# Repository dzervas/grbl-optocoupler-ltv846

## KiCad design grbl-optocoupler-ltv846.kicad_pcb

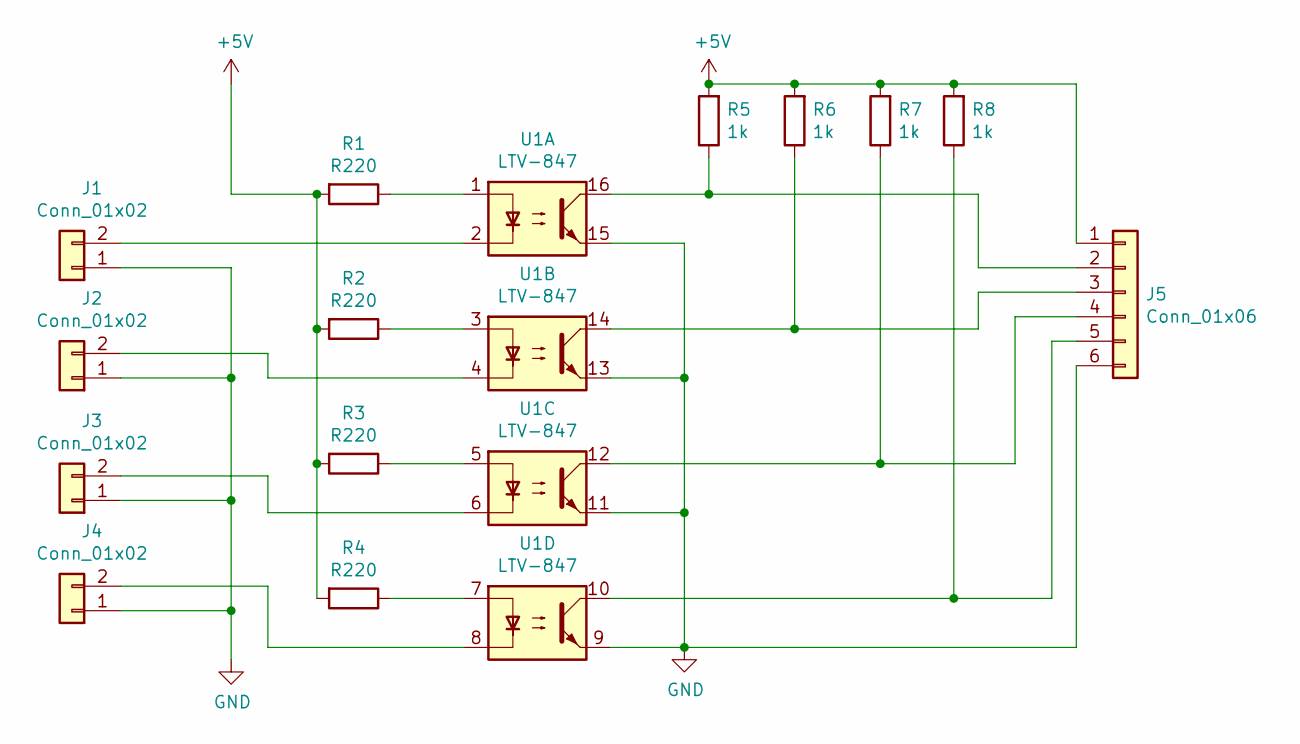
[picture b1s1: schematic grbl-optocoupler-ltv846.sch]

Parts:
J1, J2, J3, J4: Conn_01x02; PinHeader_1x02_P2.54mm_Vertical
J5: Conn_01x06; PinHeader_1x06_P2.54mm_Vertical
R1, R2, R3, R4: R220; R_Axial_DIN0207_L6.3mm_D2.5mm_P7.62mm_Horizontal
R5, R6, R7, R8: 1k; R_Axial_DIN0207_L6.3mm_D2.5mm_P7.62mm_Horizontal
U1: LTV-847; DIP-16_W7.62mm

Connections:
+5V: J5.1, R1.2, R2.2, R3.2, R4.2, R5.2, R6.2, R7.2, R8.2
GND: J1.1, J2.1, J3.1, J4.1, J5.6, U1.9, U1.11, U1.13, U1.15
unnamed: J1.2, U1.2
unnamed: J2.2, U1.4
unnamed: J3.2, U1.6
unnamed: J4.2, U1.8
unnamed: J5.2, R5.1, U1.16
unnamed: J5.3, R6.1, U1.14
unnamed: J5.4, R7.1, U1.12
unnamed: J5.5, R8.1, U1.10
unnamed: R1.1, U1.1
unnamed: R2.1, U1.3
unnamed: R3.1, U1.5
unnamed: R4.1, U1.7

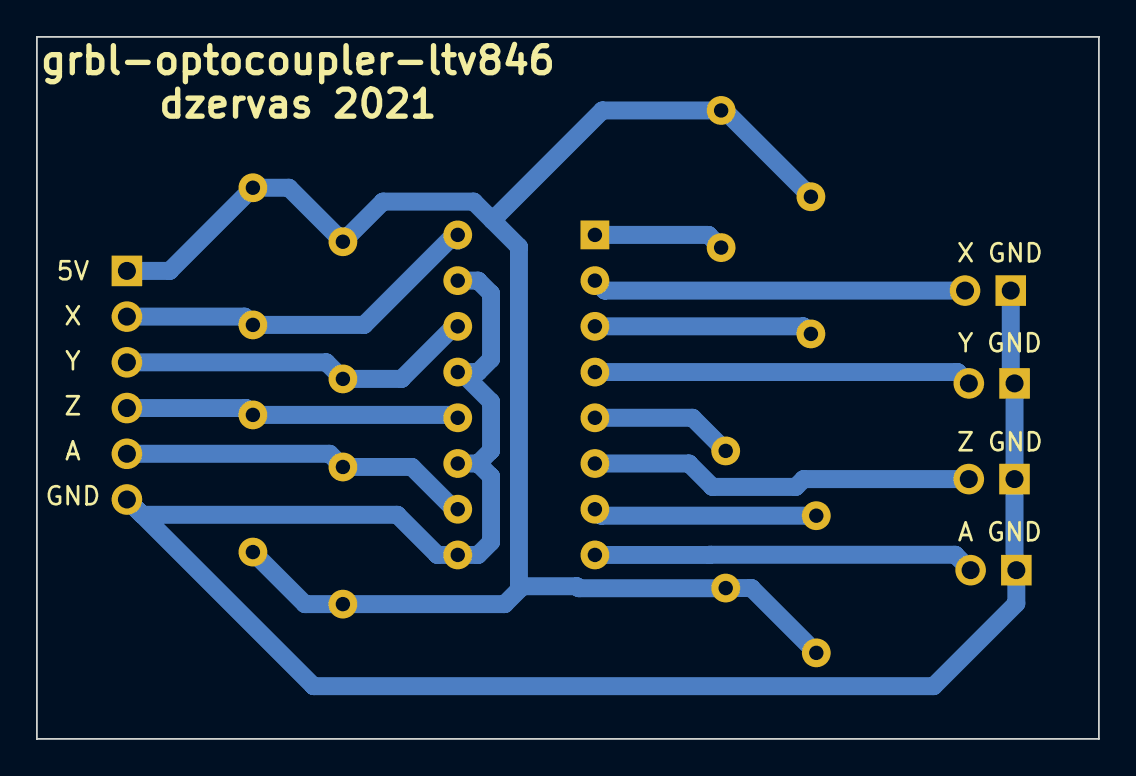
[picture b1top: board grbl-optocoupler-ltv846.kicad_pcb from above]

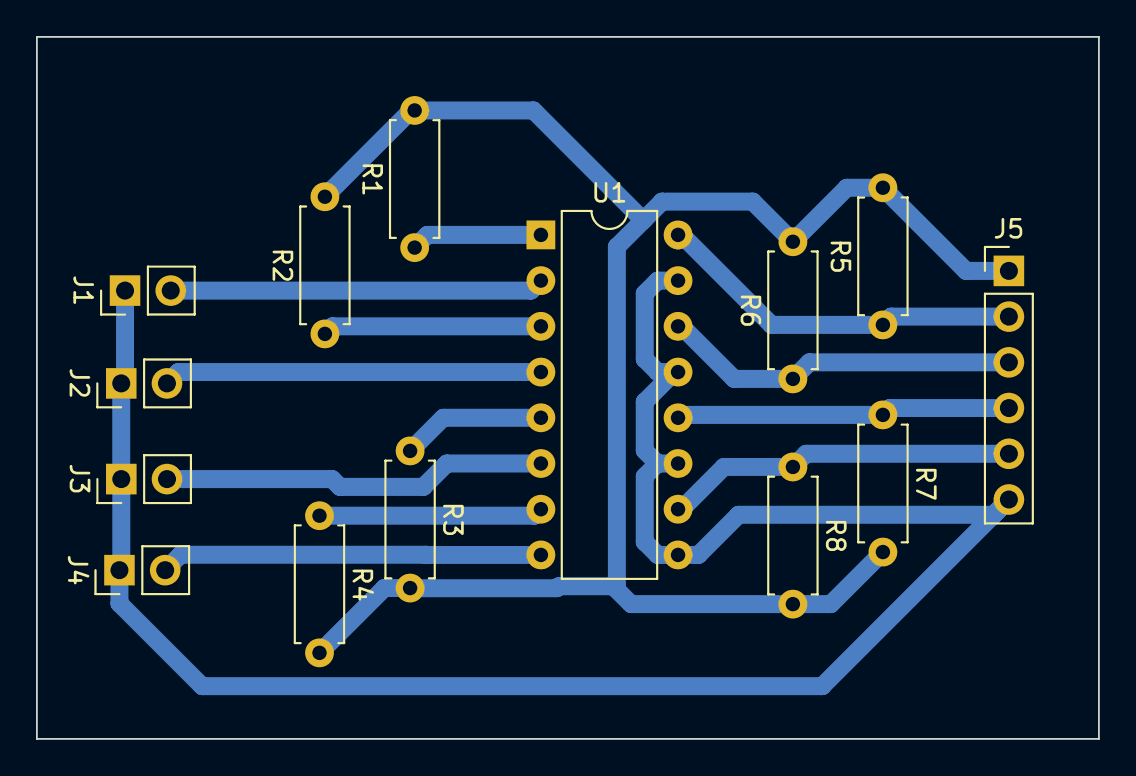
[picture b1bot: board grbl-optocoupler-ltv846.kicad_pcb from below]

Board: 2 copper layers, 59.0 x 39.0 mm, 14 parts (14 on the bottom side), 14 nets.

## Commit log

2021-10-21 Thicker traces and spacing
